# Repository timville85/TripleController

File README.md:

# 3dapter (formerly Triple Controller to USB)

This project combines the NES, SNES and Genesis DaemonBite Retro Controllers projects together with a custom PCB to support 3 different controllers with a single socketed Arduino Pro Micro. PCB (KiCad + Gerbers), 3D Cases, and muliple firmware versions (Arduino code) all available in this repository.

PCB Kits + Fully Assembled units (with firmware of your choice) available on [Tindie](https://www.tindie.com/products/24994/)

3 different firmware versions are available in this repo:
* Default: Optimized for MiSTer, PC, Raspberry Pi, etc. - reports as 3 separate controllers, supports multiplayer from a single unit.
* Analogue Pocket: Optimized for Pocket Dock - reports as a single wired XInput device.
* Nintendo Switch: Optimized for Nintendo Switch Online NES, SNES, and Genesis collections - reports as a single wired switch controller.

**Looking for a version with a N64 port? Check out the** [4dapter](https://github.com/timville85/4dapter)

## Resources Used

* [DaemonBite Retro Controllers](https://github.com/MickGyver/DaemonBite-Retro-Controllers-USB)
* https://github.com/esden/pretty-kicad-libs
* https://github.com/ddribin/nes-port-breadboard
* https://github.com/Biacco42/ProMicroKiCad
* http://www.neshq.com/hardgen/powerpad.txt

## 3D Case Files

3D Case files were designed by [Dinierto Designs](https://www.etsy.com/shop/DiniertoDesigns) and are available on [Thingiverse](https://www.thingiverse.com/thing:5011783)

3D Case Size Reference:
* 33mm - Most Micro USB Pro Micro / Sparkfun USB-C Pro Micro boards
* 35-36mm - Most AliExpress USB-C Pro Micro boards
* 36-37mm - Some AliExpress USB-C Pro Micro boards (typically with empty hole next to USB-C port)

## Wiring Diagram

Current Draw Readings from DIO Pin 16 (used for 5v supply for DB9 port):
* Krikzz Joyzz:	38mA
* 8BitDo M30 2.4G: 29mA
* OEM SEGA 3-Button Wired: 3mA
* OEM SEGA 6-Button Wired: 3mA
* Retrobit 6-Button Wired: 2mA
(Arduino DIO Max Rated Current: 40mA)

## Tested Controllers

The following controllers have been personally tested and are supported with the Triple Controller. All listed devices also fit when using the 3D Case as well.

NES:
* OEM NES Controller
* OEM NES PowerPad (Default FW Only)
* 8BitDo N30 2.4G Receiver
* 8BitDo NES Retro Receiver

SEGA / Genesis:
* OEM SEGA Master System 2-Button Controller
* OEM Genesis 3-Button Controller
* OEM Genesis 6-Button Controller
* 8BitDo M30 2.4G Receiver
* 8BitDo Genesis Retro Receiver
* Krikzz Joyzz

SNES:
* OEM SNES Controller
* OEM SFC Controller
* OEM SNES NTT Controller (Default FW Only)
* 8BitDo SN30 2.4G Receiver
* 8BitDo SNES Retro Receiver

## Bill of Materials
* **3dapter / Triple Controller PCB**

* **1x SNES Socket (90 deg):** [AliExpress - Gamers Zone Store](https://www.aliexpress.com/item/32838396935.html) 

* **1x NES Socket:** [AliExpress - Gamers Zone Store](https://www.aliexpress.com/item/1005003699734963.html)

* **1x Genesis Socket:** [AliExpress - Gamers Zone Store](https://www.aliexpress.com/item/1005003699497865.html)

* **Micro USB Arduino Pro Micro (reinforced USB port):** [Amazon](https://www.amazon.com/gp/product/B01HCXMBOU/) *(Pack of 3)*

* **1x Arduino Pro Micro (USB-C 3-15V Version):** [AliExpress](https://www.aliexpress.us/item/2251832700923799.html)

* **2x 1x12 Female Header:** [Digi-Key](https://www.digikey.com/en/products/detail/sullins-connector-solutions/PPTC121LFBN-RC/807231)

## PCB + Assembled Examples

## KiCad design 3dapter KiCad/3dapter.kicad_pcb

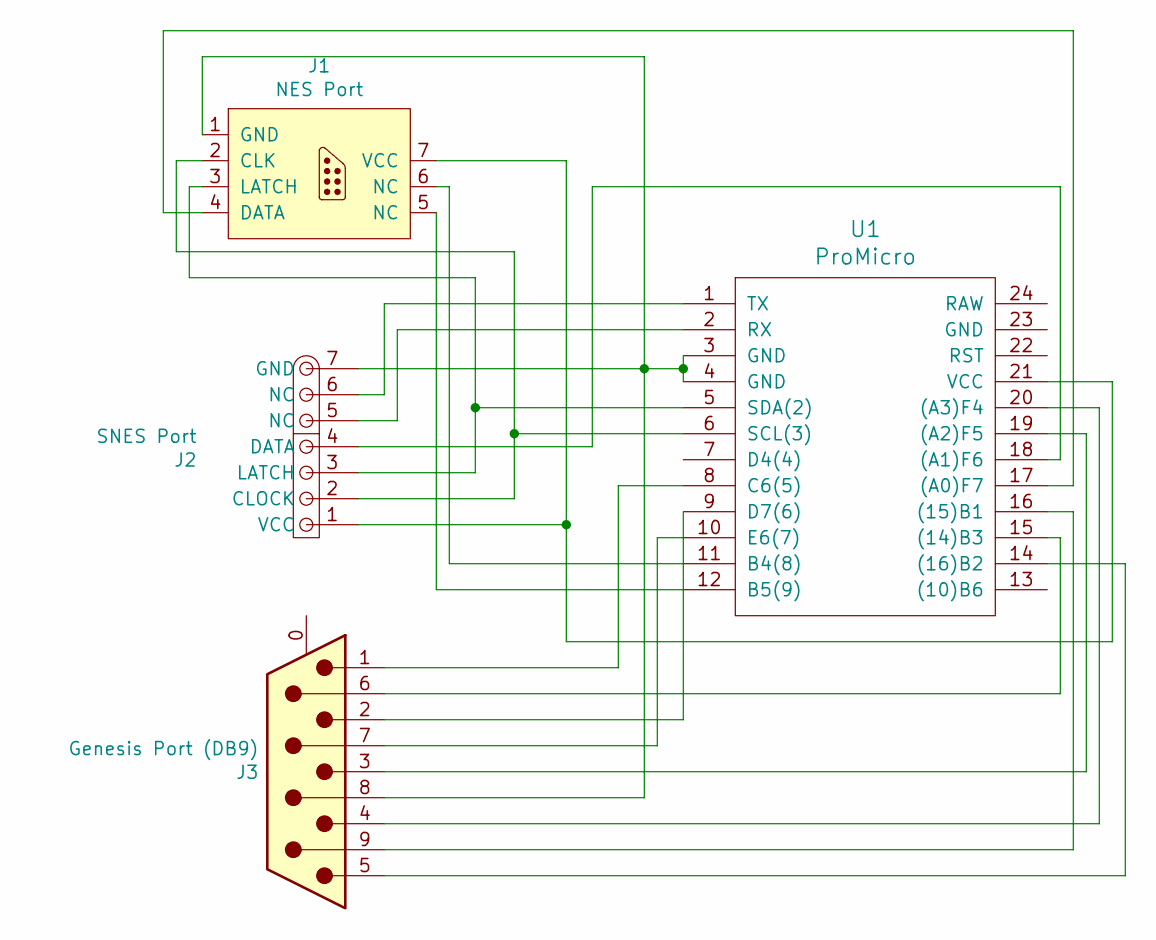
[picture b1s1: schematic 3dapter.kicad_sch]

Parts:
J1: NES Port; NES
J2: SNES Port; SNES
J3: Genesis Port (DB9); DSUB-9_Male_Horizontal_P2.77x2.54mm_EdgePinOffset9.40mm
U1: ProMicro

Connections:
unnamed: J1.1 (GND), J2.7 (GND), J3.8, U1.3 (GND), U1.4 (GND)
unnamed: J1.2 (CLK), J2.2 (CLOCK), U1.6 (SCL(3))
unnamed: J1.3 (LATCH), J2.3 (LATCH), U1.5 (SDA(2))
unnamed: J1.4 (DATA), U1.17 ((A0)F7)
unnamed: J1.5 (NC), U1.12 (B5(9))
unnamed: J1.6 (NC), U1.11 (B4(8))
unnamed: J1.7 (VCC), J2.1 (VCC), U1.21 (VCC)
unnamed: J2.4 (DATA), U1.18 ((A1)F6)
unnamed: J2.5 (NC), U1.2 (RX)
unnamed: J2.6 (NC), U1.1 (TX)
unnamed: J3.1, U1.8 (C6(5))
unnamed: J3.2, U1.9 (D7(6))
unnamed: J3.3, U1.19 ((A2)F5)
unnamed: J3.4, U1.20 ((A3)F4)
unnamed: J3.5, U1.14 ((16)B2)
unnamed: J3.6, U1.15 ((14)B3)
unnamed: J3.7, U1.10 (E6(7))
unnamed: J3.9, U1.16 ((15)B1)

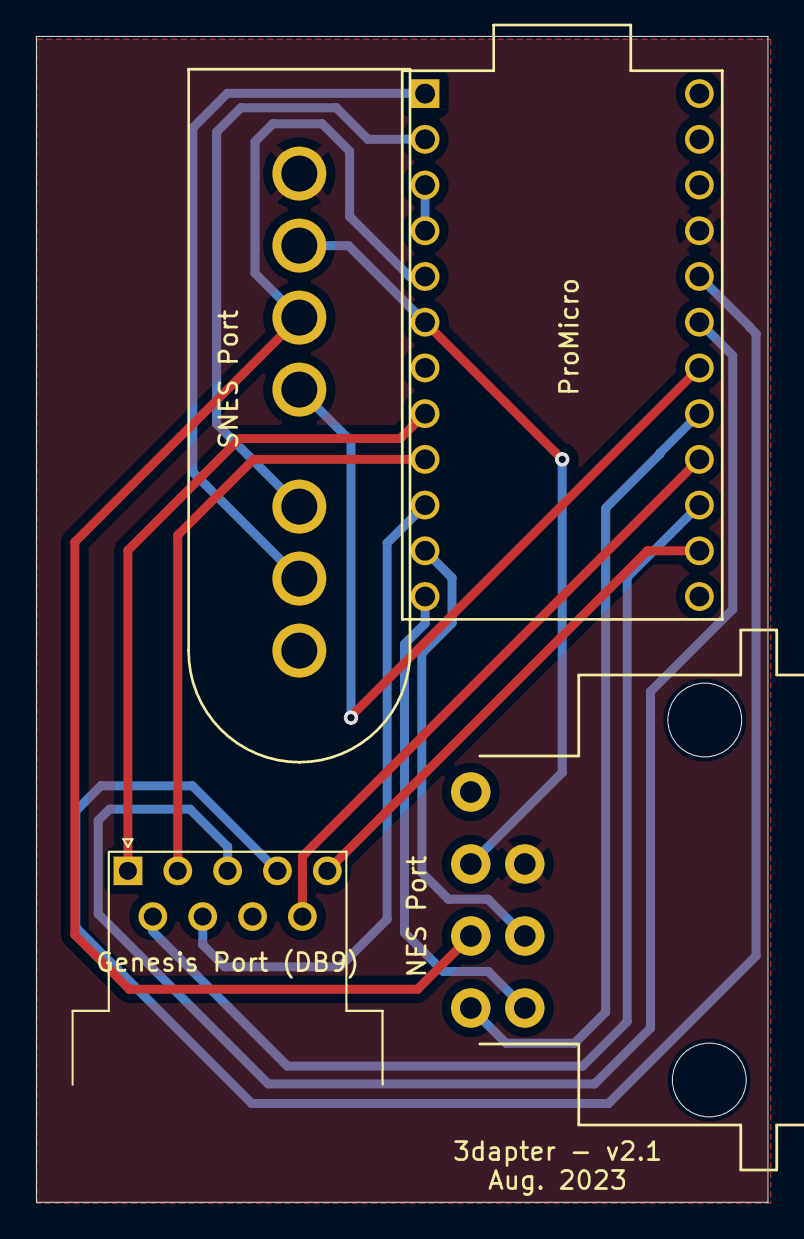
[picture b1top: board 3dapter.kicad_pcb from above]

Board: 2 copper layers, 40.6 x 64.8 mm, 4 parts (0 on the bottom side), 18 nets.

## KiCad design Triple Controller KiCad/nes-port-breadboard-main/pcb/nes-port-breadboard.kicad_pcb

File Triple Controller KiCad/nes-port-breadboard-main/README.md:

# NES Port Breadboard Adapter

A breadboard adapter for a console-side (male) NES port, specifically the [Raphnet right-angle NES controller connector][1].

Top of PCB:

Bottom of PCB:

[1]: https://www.raphnet-tech.com/products/nes_controller_connector/index.php

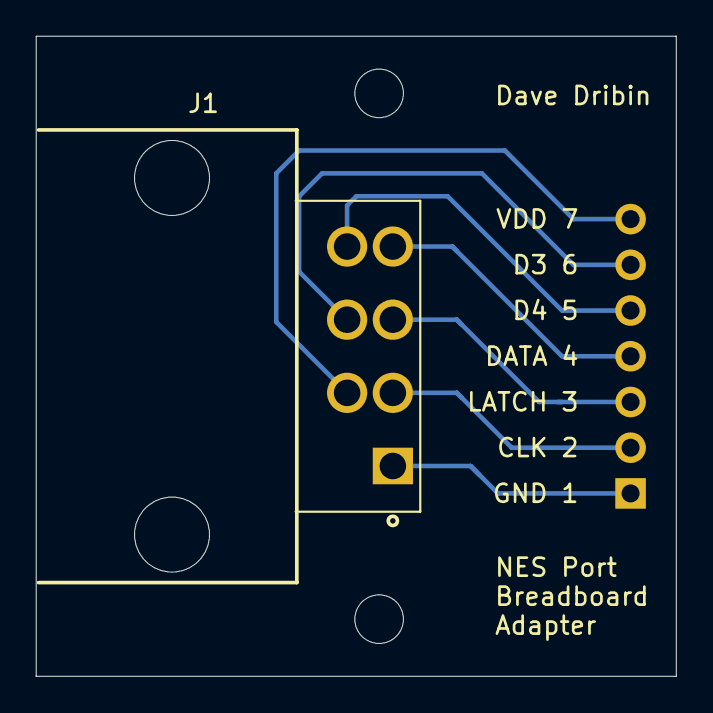
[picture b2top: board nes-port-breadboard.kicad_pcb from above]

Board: 2 copper layers, 35.6 x 35.6 mm, 4 parts (1 on the bottom side), 7 nets.

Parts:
H1, H2: MountingHole; MountingHole_2.7mm_M2.5
J1: NES_Port_Male; NES_Port_Male_Horizontal
J2: Conn_01x07; PinHeader_1x07_P2.54mm_Vertical

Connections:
/CLK: J1.2, J2.2
/D3: J1.6, J2.6
/D4: J1.5, J2.5
/DATA: J1.4, J2.4
/GND: J1.1, J2.1
/LATCH: J1.3, J2.3
/VDD: J1.7, J2.7

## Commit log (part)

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2021-08-18 Initial Upload
2021-08-18 Fix 6-button controller issue
2021-08-18 Updating Readme and Button Layouts
2021-08-19 Timing Chart for Main Loop + Small Code Cleanup
2021-08-20 Aligned Genesis Buttons to NES/SNES
2021-08-22 Added initial KiCad PCB Project / Outputs
2021-09-08 Add files via upload
    Complete revamp of PCB due to incorrect pin layout
2021-10-06 Resolve Issue with SNES to Genesis Mapping
    Reordered buttons for Genesis for zero reconfig mapping
2021-10-11 Added 3D Model Files
    3D STL and STEP files - courtesy of Dinierto Designs
2021-10-12 Small case revision
2021-10-16 Rename Triple_Controller_Adapter_Bottom.step.txt to Triple_Controller_Adapter_Bottom.step
2021-10-16 Rename Triple_Controller_Adapter_Top.step.txt to Triple_Controller_Adapter_Top.step
2021-10-29 New case revisions - added Sparkfun USB-C
2021-11-27 New Arduino Project to support SNES NTT Controller
2021-11-27 Small comment updates
2021-11-27 Small tweak based on MR + extra comment
2021-11-29 Updated links
2021-12-03 Adding initial V2 PCB Code
2021-12-03 Adding V2 PCB KiCad Project
2021-12-03 Bug fixes across all projects
2021-12-04 Fix NES Controller issue
2021-12-04 Small bug fixes + MiSTer MAP Files
2021-12-04 Add MiSTer MAP Files
2021-12-05 Timing optimizations for consistent packets
2021-12-05 Continued code cleanup and loop optimization
2021-12-27 New Experimental Firmware for V1 and V2 Boards
2022-01-19 Combined V1 and V2 together to V2.1 PCB
2022-02-02 Updated AliExpress links for lower minimum quantities
2022-04-11 Align Genesis input to SNES/NES
2022-04-17 Remap Genesis Buttons
2022-04-18 Fix pinout comments
2022-04-18 Updated Docs
2022-08-21 Added Pre-Configured Map File
2022-09-11 Add Makefile to build and upload with arduino-cli
2022-09-11 Implement profiles for the Genesis controller
    The Genesis controller can now be in two different modes if using
    an 8bitdo controller.
    1. MiSTer mode
    - The home button sends "DOWN + MODE"
    (This is because no equivalent of the home button exists
    on the other controller ports and MiSTer require they button
2022-10-17 Fix Arduino Compiler Warning
2022-12-28 Cleaning up 3D Case files
2022-12-28 Reorganized 3D Case files
2023-01-06 Add New Arduino Code for XInput Version
    Provides Analogue Pocket Dock compatibility (all 3 inputs share and appear as a single input)
2023-01-06 Fix multi-send issue
2023-01-07 Added benchmarking comments to XInput Library for Pocket + MiSTer
2023-08-20 Rebrand project and add new files
2023-09-16 Modified N64 value mapping logic
    Modified N64 value mapping logic to set condition to switch between N64 controller raw value and HID 8-bit max (-128 to +127)
2023-09-16 Revert wrong update

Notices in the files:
Triple Controller KiCad/nes-port-breadboard-main/pcb/nes-port-breadboard.kicad_pcb:
MIT License
